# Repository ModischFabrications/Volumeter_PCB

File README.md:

# Volumeter_PCB

This is a KiCad project that models the main PCB for a Volume Display. Code and CAD-files will be managed separately.

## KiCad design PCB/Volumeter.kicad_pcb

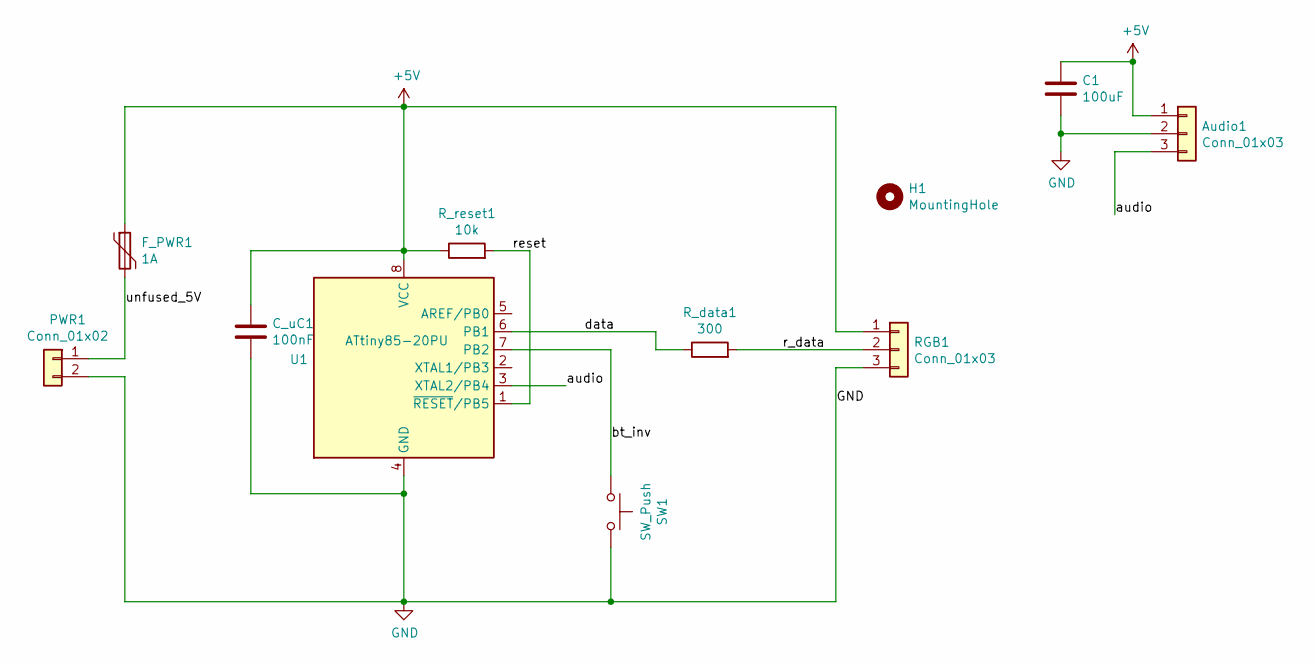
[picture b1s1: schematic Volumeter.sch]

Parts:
Audio1: Conn_01x03; PinSocket_1x03_P2.54mm_Horizontal
C1: 100uF; CP_Radial_D5.0mm_P2.50mm
C_uC1: 100nF; C_0603_1608Metric
F_PWR1: 1A; Fuse_1206_3216Metric
H1: MountingHole; MountingHole_3.2mm_M3_ISO14580
PWR1: Conn_01x02; PinHeader_1x02_P2.54mm_Vertical
RGB1: Conn_01x03; JST_XH_S3B-XH-A_1x03_P2.50mm_Horizontal
R_data1: 300; R_0603_1608Metric
R_reset1: 10k; R_0603_1608Metric
SW1: SW_Push; SW_PUSH_6mm_H4.3mm
U1: ATtiny85-20PU; DIP-8_W7.62mm

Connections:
+5V: Audio1.1, C1.1, C_uC1.1, F_PWR1.1, RGB1.1, R_reset1.1, U1.8 (VCC)
/audio: Audio1.3, U1.3 (XTAL2/PB4)
/bt_inv: SW1.1, U1.7 (PB2)
/data: R_data1.1, U1.6 (PB1)
/r_data: RGB1.2, R_data1.2
/reset: R_reset1.2, U1.1 (~RESET~/PB5)
/unfused_5V: F_PWR1.2, PWR1.1
GND: Audio1.2, C1.2, C_uC1.2, PWR1.2, RGB1.3, SW1.2, U1.4 (GND)

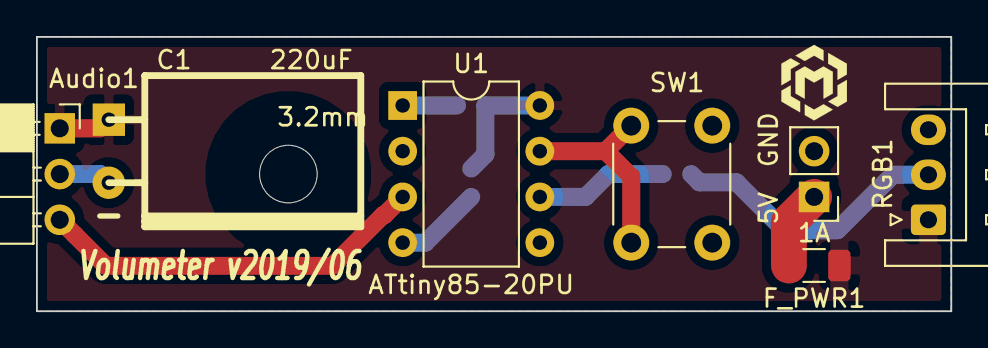
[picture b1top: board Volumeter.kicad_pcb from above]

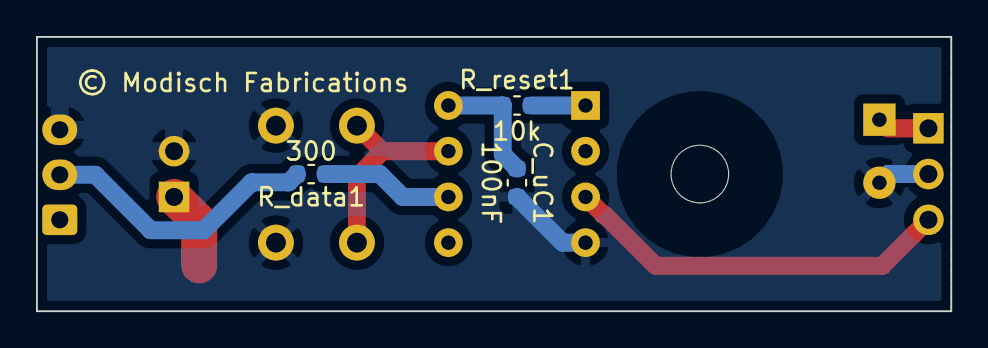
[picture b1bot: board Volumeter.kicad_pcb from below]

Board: 2 copper layers, 50.8 x 15.2 mm, 11 parts (3 on the bottom side), 8 nets.

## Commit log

2019-03-30 rev.1 with power on the outside and MAX4466
2019-03-30 switched PWR & LED
2019-04-02 added mounting holes and played around
2019-04-25 use official kicad gitignore, (re)move Gerber
2019-04-25 fixed gitignore
2019-04-25 fixed gitignore again
2019-04-25 added 100nF ceramic, streamlined reset
2019-04-26 added version, name; improved connector to horizontal
2019-04-28 noted wrong polarity, moved SMD to backside
2019-06-10 moved breadboard to separate folder
2019-06-10 created PCB version
2019-06-10 add images
2019-06-10 improve label placement
2019-06-10 add LFS
2019-06-10 moved to root and refined lfs file
2019-06-10 fix labels, move power labels
2019-06-10 name Volumeter v2019/06, add logo
2019-06-10 use fake R package for fuse
2019-06-10 renamed project to volumeter
2019-06-10 rename breadboard to volumeter as well
2019-06-10 remove hole label
2019-06-10 use horizontal capacitor model
2019-06-10 update render
2019-06-11 use line cuts instead of polygons, create step
2019-06-11 update screenshots
2019-06-11 exclude step and gerber
2019-06-11 don't track step
2019-06-11 show all layers
2019-06-11 move pictures to /pictures
2019-06-11 add schematic picture
2019-06-11 increase hole clearance
2019-06-11 shuffle wires around

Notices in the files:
PCB/Volumeter.kicad_pcb:
© Modisch Fabrications
